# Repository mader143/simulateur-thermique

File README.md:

# Simulateur Thermique
# Équipe 5 (Da best)

## Description

Simulateur thermique 2D pour modéliser la diffusion de chaleur dans une plaque métallique. Le projet regroupe une simulation numérique en Python avec interface graphique PyQt5, une simulation du système et du régulateur via Simulink (Matlab), du code Arduino pour l'acquisition et la régulation d'un prototype réel, et les données expérimentales pour la validation des différents paramètres identifiés.

## Contenu du projet

**Simulation Python** : Résolution par différences finies de l'équation de diffusion thermique, interface utilisateur interactive, génération de résultats et animations.

**Simulation Simulink** : Division du système/procédé en sous-systèmes et identification des fonctions de transfert de ceux-ci. Ajout d'un régulateur PID pour valider la commande contrôlant le prototype.

**Code Arduino** : Contrôleur PID pour régulation thermique, conditionnement des signaux, identification expérimentale, enregistrement des données.

**Conception PCB** : Schémas et circuits imprimés KiCad avec Arduino Mega 2560, amplificateurs opérationnels, et conditionnement analogique pour la lecture de la température en trois points sur la plaque métallique.

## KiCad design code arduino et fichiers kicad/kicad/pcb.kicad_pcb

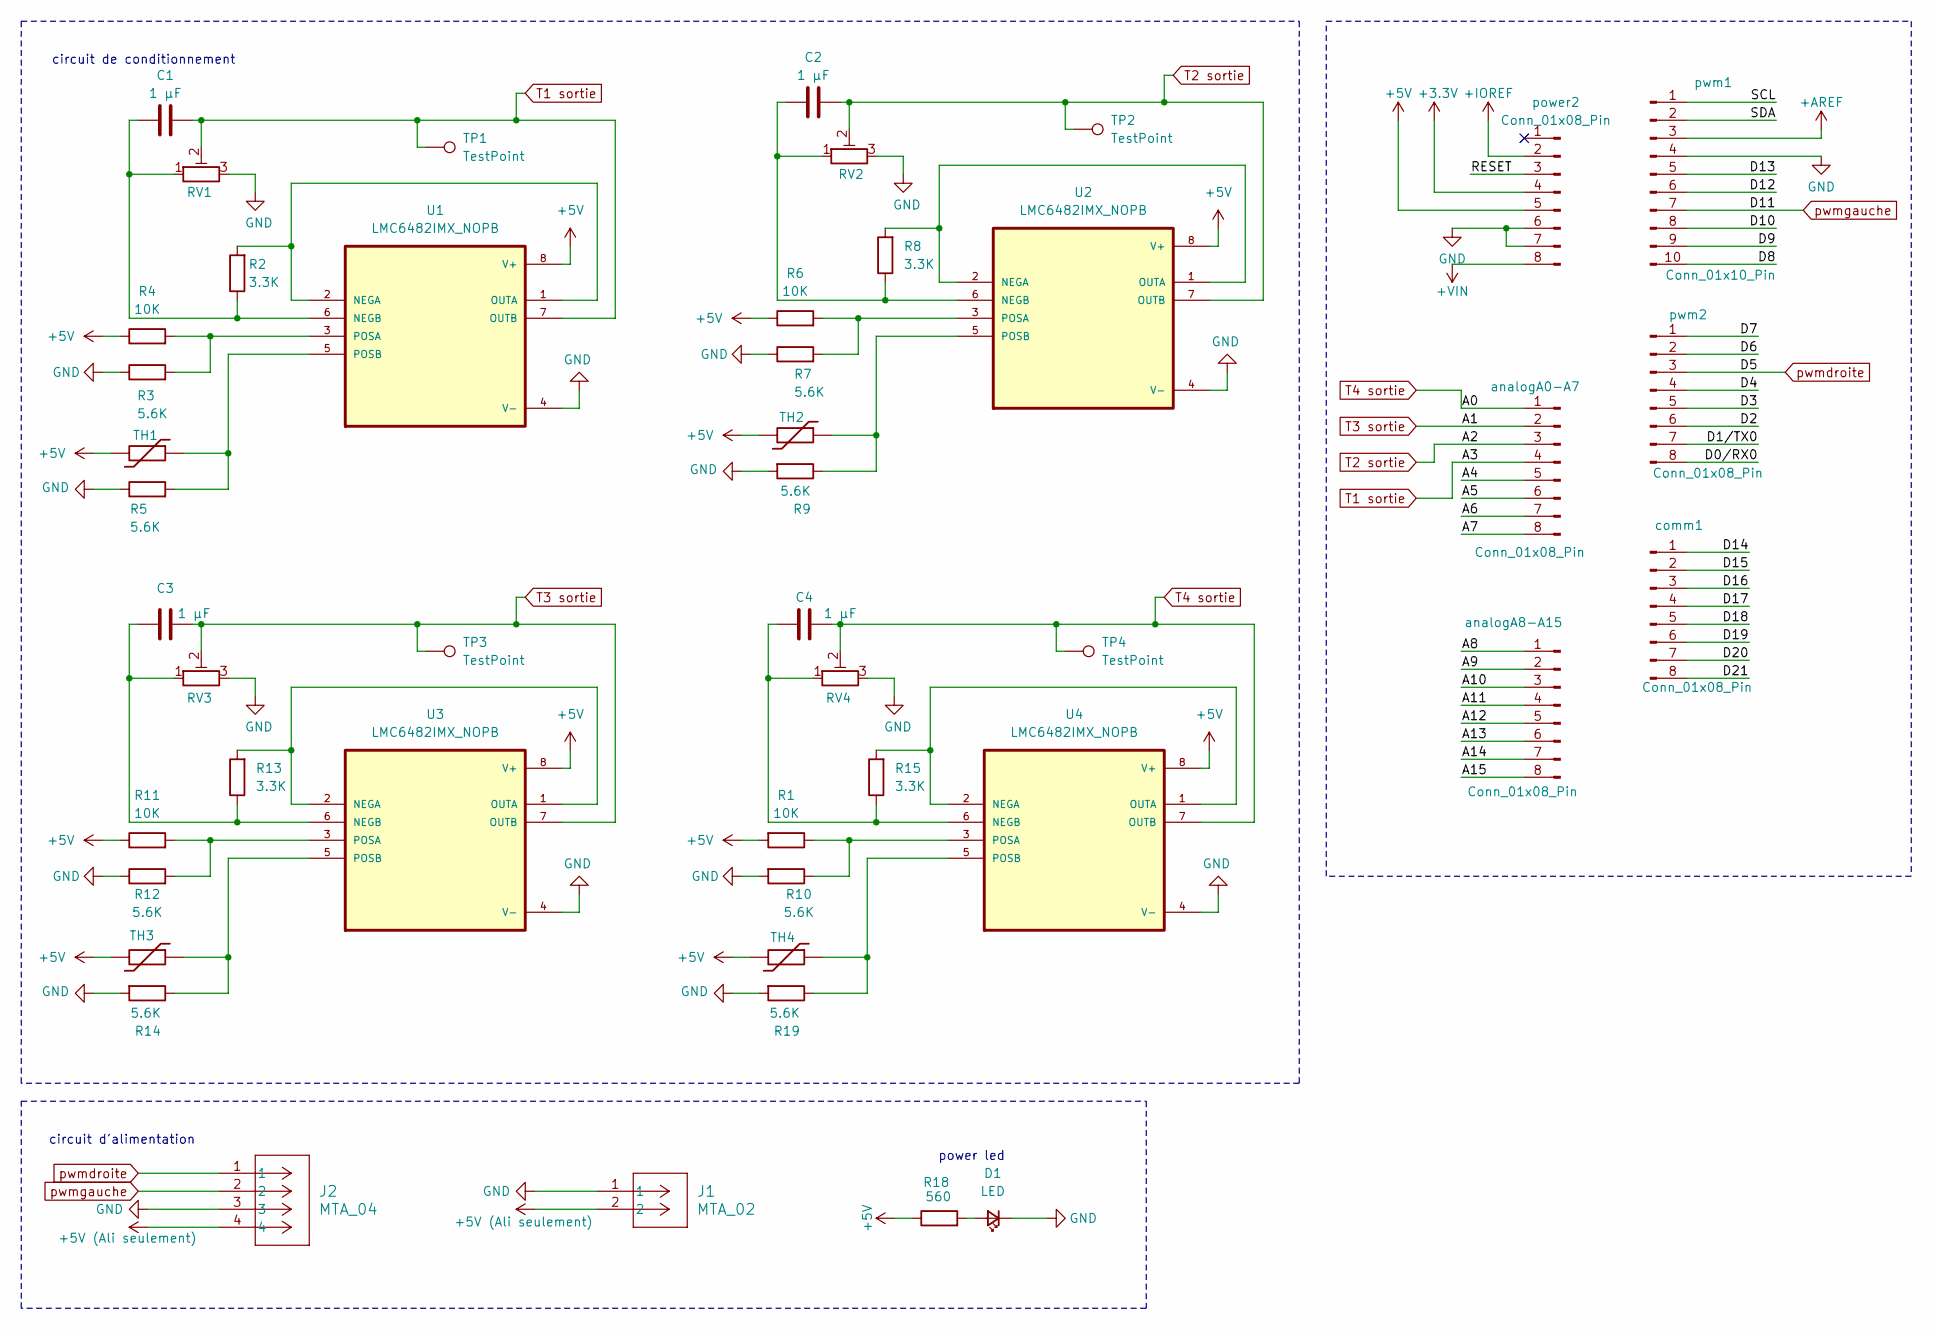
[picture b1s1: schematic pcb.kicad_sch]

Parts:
C1, C2, C3, C4: 1 μF; condensateur 1uF
D1: LED; LED_D5.0mm
J1: MTA_02; MTA_CONN2_640445-2
J2: MTA_04; MTA_CONN4_640445-4
R1, R4, R6, R11: 10K; Resistance SMT
R2, R8, R13, R15: 3.3K; Resistance SMT
R3, R5, R7, R9, R10, R12, R14, R19: 5.6K; Resistance SMT
R18: 560; Resistance SMT
RV1, RV2, RV3, RV4: R_Potentiometer_Trim; trimpot
TH1, TH2, TH3, TH4: Screw_Terminal_01x02; MTA_CONN2_640445-2
TP1, TP2, TP3, TP4: TestPoint; TestPoint_THTPad_D1.5mm_Drill0.7mm
U1, U2, U3, U4: LMC6482IMX_NOPB; LMC6482_SMT
analogA0-A7, analogA8-A15: Conn_01x08_Pin; PinHeader_1x08_P2.54mm_Vertical
comm1: Conn_01x08_Pin; PinHeader_1x08_P2.54mm_Vertical
power2: Conn_01x08_Pin; PinHeader_1x08_P2.54mm_Vertical
pwm1: Conn_01x10_Pin; PinHeader_1x10_P2.54mm_Vertical
pwm2: Conn_01x08_Pin; PinHeader_1x08_P2.54mm_Vertical

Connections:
+3.3V: power2.4
+5V: R1.2, R4.1, R6.1, R11.1, R18.1, TH1.2, TH2.2, TH3.2, TH4.2, U1.8 (V+), U2.8 (V+), U3.8 (V+), U4.8 (V+), power2.5
+5V (Ali seulement): J1.2, J2.4
+AREF: pwm1.3
+IOREF: power2.2
+VIN: power2.8
/A4: analogA0-A7.5
/A5: analogA0-A7.6
/A6: analogA0-A7.7
/A7: analogA0-A7.8
/A8: analogA8-A15.1
/A9: analogA8-A15.2
/A10: analogA8-A15.3
/A11: analogA8-A15.4
/A12: analogA8-A15.5
/A13: analogA8-A15.6
/A14: analogA8-A15.7
/A15: analogA8-A15.8
/D0/RX0: pwm2.8
/D1/TX0: pwm2.7
/D2: pwm2.6
/D3: pwm2.5
/D4: pwm2.4
/D6: pwm2.2
/D7: pwm2.1
/D8: pwm1.10
/D9: pwm1.9
/D10: pwm1.8
/D12: pwm1.6
/D13: pwm1.5
/D14: comm1.1
/D15: comm1.2
/D16: comm1.3
/D17: comm1.4
/D18: comm1.5
/D19: comm1.6
/D20: comm1.7
/D21: comm1.8
/RESET: power2.3
/SCL: pwm1.1
/SDA: pwm1.2
GND: D1.1 (K), J1.1, J2.3, R3.1, R5.1, R7.1, R9.2, R10.2, R12.1, R14.2, R19.2, RV1.3, RV2.3, RV3.3, RV4.3, U1.4 (V-), U2.4 (V-), U3.4 (V-), U4.4 (V-), power2.6, power2.7, pwm1.4
unnamed: D1.2 (A), R18.2
unnamed: R2.2, U1.1 (OUTA), U1.2 (NEGA)
unnamed: C1.1, R2.1, RV1.1, U1.6 (NEGB)
unnamed: R3.2, R4.2, U1.3 (POSA)
unnamed: R5.2, TH1.1, U1.5 (POSB)
unnamed: R8.2, U2.1 (OUTA), U2.2 (NEGA)
unnamed: C2.1, R8.1, RV2.1, U2.6 (NEGB)
unnamed: R6.2, R7.2, U2.3 (POSA)
unnamed: R9.1, TH2.1, U2.5 (POSB)
unnamed: R13.2, U3.1 (OUTA), U3.2 (NEGA)
unnamed: C3.1, R13.1, RV3.1, U3.6 (NEGB)
unnamed: R11.2, R12.2, U3.3 (POSA)
unnamed: R14.1, TH3.1, U3.5 (POSB)
unnamed: R15.2, U4.1 (OUTA), U4.2 (NEGA)
unnamed: C4.1, R15.1, RV4.1, U4.6 (NEGB)
unnamed: R1.1, R10.1, U4.3 (POSA)
unnamed: R19.1, TH4.1, U4.5 (POSB)
T1 sortie: C1.2, RV1.2, TP1.1, U1.7 (OUTB), analogA0-A7.4
T2 sortie: C2.2, RV2.2, TP2.1, U2.7 (OUTB), analogA0-A7.3
T3 sortie: C3.2, RV3.2, TP3.1, U3.7 (OUTB), analogA0-A7.2
T4 sortie: C4.2, RV4.2, TP4.1, U4.7 (OUTB), analogA0-A7.1
pwmdroite: J2.1, pwm2.3
pwmgauche: J2.2, pwm1.7

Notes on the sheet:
circuit d'alimentation
power led
circuit de conditionnement

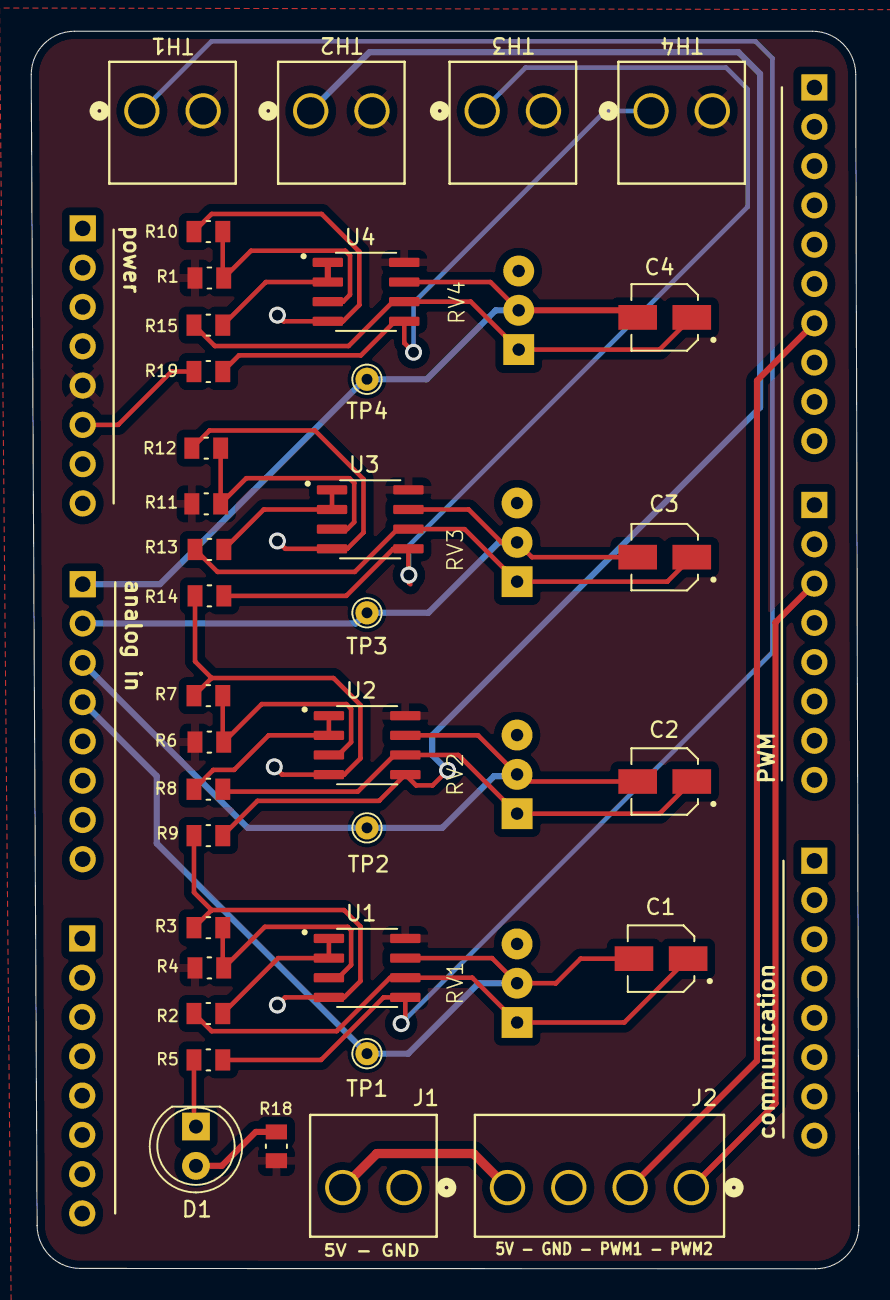
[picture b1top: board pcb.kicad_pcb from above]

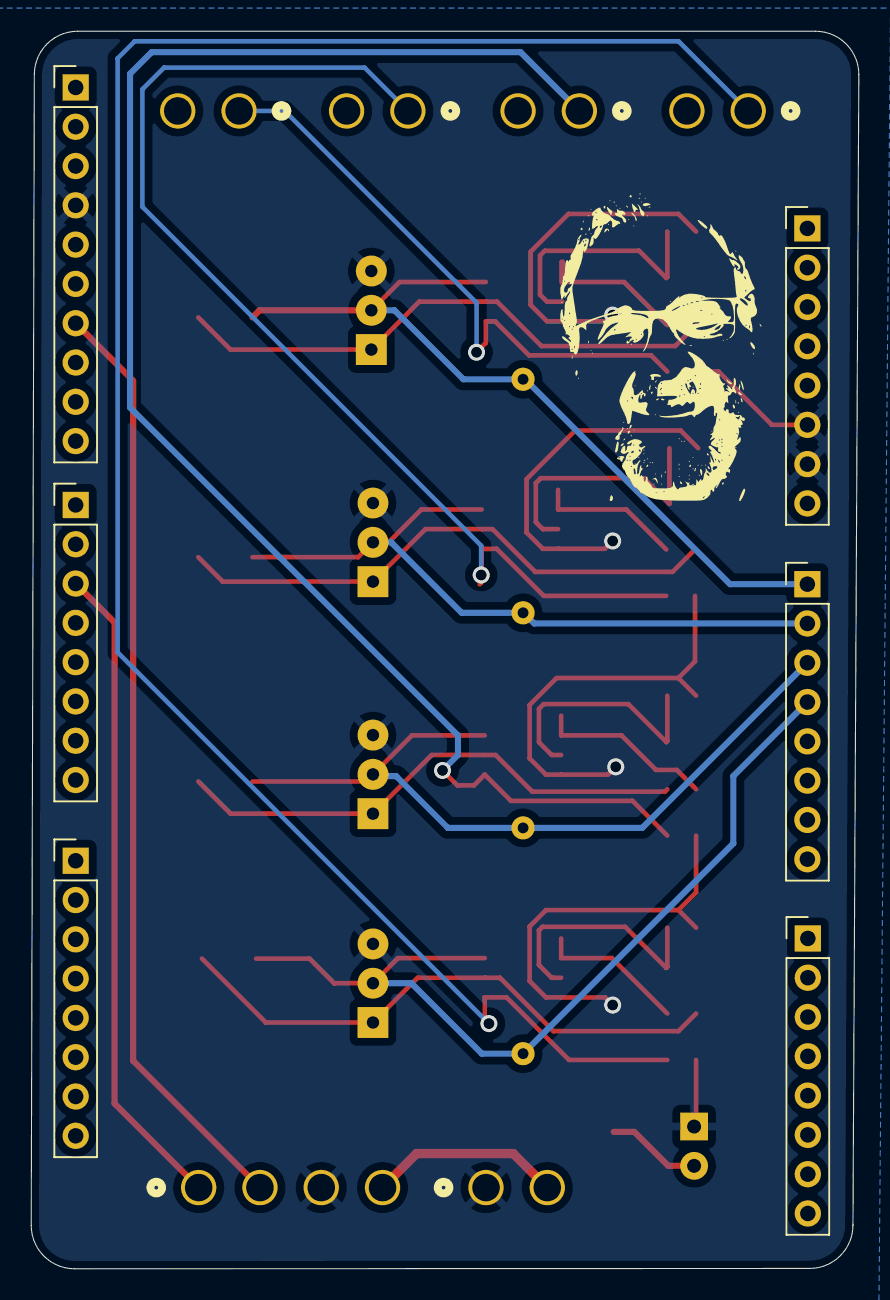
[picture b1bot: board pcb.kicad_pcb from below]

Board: 2 copper layers, 53.5 x 80.0 mm, 46 parts (6 on the bottom side), 26 nets.

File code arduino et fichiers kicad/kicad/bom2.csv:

"Id";"Référence";"Empreinte";"Quantité";"Désignation";"Fournisseur et réf";
1;"RV3,RV2,RV4,RV1";"trimpot";4;"R_Potentiometer_Trim";;;
2;"J1";"MTA_CONN2_640445-2";1;"MTA_02";;;
3;"R6,R4,R11,R1";"Resistance SMT";4;"10K";;;
4;"R3,R10,R14,R9,R5,R19,R7,R12";"Resistance SMT";8;"5.6K";;;
5;"C1,C4,C2,C3";"condensateur 1uF";4;"1 μF";;;
6;"TH3,TH2,TH4,TH1";"MTA_CONN2_640445-2";4;"Screw_Terminal_01x02";;;
7;"D1";"LED_D5.0mm";1;"LED";;;
8;"U1,U3,U2,U4";"LMC6482_SMT";4;"LMC6482IMX_NOPB";;;
9;"R8,R2,R13,R15";"Resistance SMT";4;"3.3K";;;
10;"R18";"Resistance SMT";1;"560";;;
11;"J2";"MTA_CONN4_640445-4";1;"MTA_04";;;
12;"power2,analogA0-A7,comm1,analogA8-A15,pwm2";"PinHeader_1x08_P2.54mm_Vertical";5;"Conn_01x08_Pin";;;
13;"pwm1";"PinHeader_1x10_P2.54mm_Vertical";1;"Conn_01x10_Pin";;;

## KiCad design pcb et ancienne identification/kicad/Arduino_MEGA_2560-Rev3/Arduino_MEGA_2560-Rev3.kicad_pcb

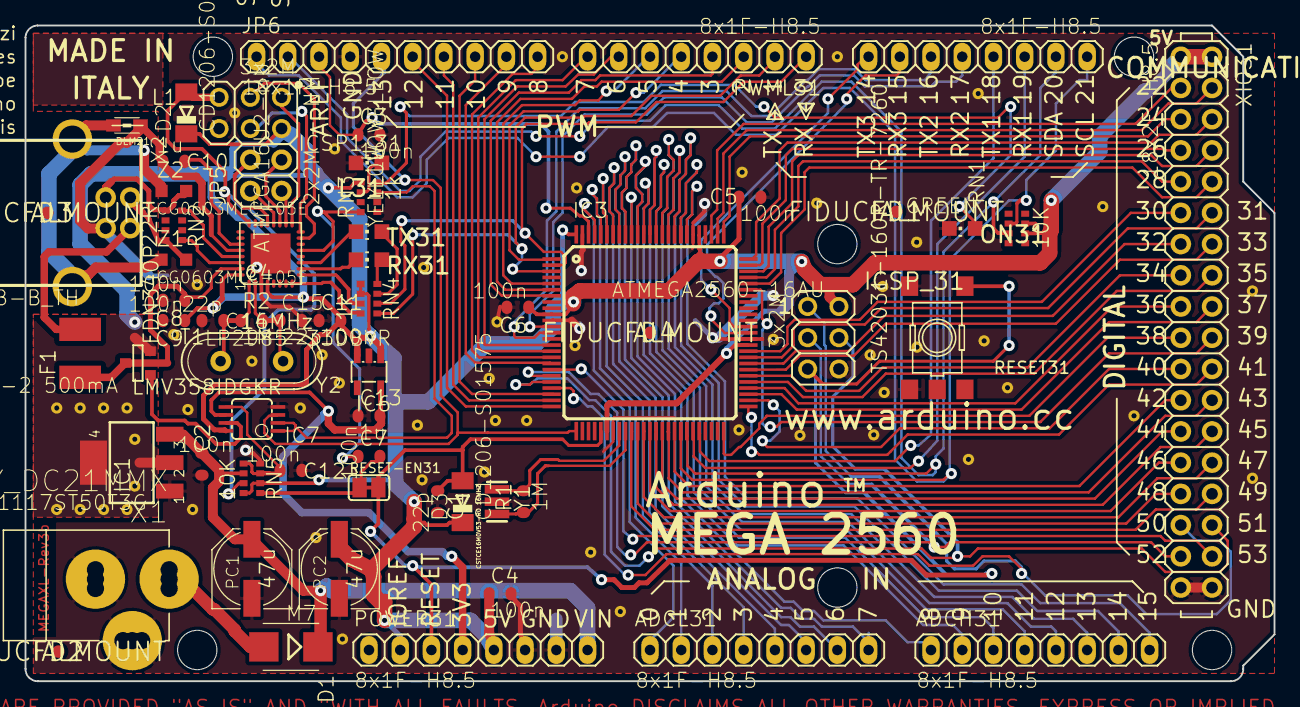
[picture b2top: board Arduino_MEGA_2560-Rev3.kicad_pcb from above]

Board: 2 copper layers, 101.6 x 53.3 mm, 69 parts (1 on the bottom side), 110 nets.

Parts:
@HOLE0, @HOLE1, @HOLE2, @HOLE3, @HOLE4, @HOLE5: (no value)
ADCH31: 8x1F-H8.5; 1X08
ADCL31: 8x1F-H8.5; 1X08
C1, C14, C15: 22p; C0603-ROUND
C2, C3, C4, C5, C6, C7, C8, C9, C11, C12: 100n; C0603-ROUND
C10, C13: 1u; C0603-ROUND
COMMUNICATION31: 8x1F-H8.5; 1X08
D1: M7; SMB
D2, D3: CD1206-S01575; MINIMELF
F1: MF-MSMF050-2 500mA; L1812
FD1, FD2, FD3, FD4: FIDUCIALMOUNT; FIDUCIA-MOUNT
GROUND31: SJ
IC1: NCP1117ST50T3G; SOT223
IC3: ATMEGA2560-16AU; TQFP100
IC4: ATMEGA16U2-MU; MLF32
IC6: LP2985-33DBVR; SOT23-DBV
IC7: LMV358IDGKR; MSOP08
ICSP1_31: 3x2M; 2X03
ICSP_31: 3x2M; 2X03
JP5: 2x2M - NM; 2X02
JP6: 10x1F-H8.5; 1X10
L1: BLM21; 0805
L31: YELLOW; CHIP-LED0805
ON31: GREEN; CHIP-LED0805
PC1, PC2: 47u; PANASONIC_D
POWER31: 8x1F-H8.5; 1X08
PWML31: 8x1F-H8.5; 1X08
R1, R2: 1M; R0603-ROUND
RESET31: TS42031-160R-TR-7260; TS42
RESET-EN31: SJ
RN1, RN5: 10K; CAT16
RN2: 22R; CAY16
RN3, RN4: 1k; CAY16
RX31: YELLOW; CHIP-LED0805
T1: FDN340P; SOT-23
TX31: YELLOW; CHIP-LED0805
U$1: DISCLAIMER
X1: POWERSUPPLY_DC21MMX; POWERSUPPLY_DC-21MM
X2: USB-B_TH; PN61729
XIO31: 18x2F-H8.5; 2X18
Y1: CSTCE16M0V53-R0 16MHZ; RESONATOR
Y2: 16MHz; QS
Z1, Z2: CG0603MLC-05E; CT%2fCN0603

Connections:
+3V3: C13.2, IC6.5, IC7.6, POWER31.4
+5V: C4.1, C5.1, C6.1, C9.1, C11.2, D2.C, D3.C, IC1.2, IC1.4, IC3.10, IC3.31, IC3.61, IC3.80, IC3.100, IC4.4, IC4.32, IC6.1, IC6.3, IC7.8, ICSP1_31.2, ICSP_31.2, PC2.+, POWER31.2, POWER31.5, RN1.6, RN1.7, RN3.1, RN4.5, RN4.6, RN5.2, RN5.8, T1.2, XIO31.1, XIO31.2
/8PB4: IC4.18, JP5.1
/8PB5: IC4.19, JP5.3
/8PB6: IC4.20, JP5.2
/8PB7: IC4.21, JP5.4
/ADC0: ADCL31.1, IC3.97
/ADC1: ADCL31.2, IC3.96
/ADC2: ADCL31.3, IC3.95
/ADC3: ADCL31.4, IC3.94
/ADC4: ADCL31.5, IC3.93
/ADC5: ADCL31.6, IC3.92
/ADC6: ADCL31.7, IC3.91
/ADC7: ADCL31.8, IC3.90
/ADC8: ADCH31.1, IC3.89
/ADC9: ADCH31.2, IC3.88
/ADC10: ADCH31.3, IC3.87
/ADC11: ADCH31.4, IC3.86
/ADC12: ADCH31.5, IC3.85
/ADC13: ADCH31.6, IC3.84
/ADC14: ADCH31.7, IC3.83
/ADC15: ADCH31.8, IC3.82
/AREF: C3.1, IC3.98, JP6.3
/CMP: C12.2, IC7.5, RN5.3, RN5.5
/D+: RN2.5, X2.3, Z2.2
/D-: RN2.8, X2.2, Z1.2
/DTR: C7.1, IC4.13, RN3.4
/GATE_CMD: IC7.7, T1.3
/L13: IC7.1, IC7.2, RN3.7
/M8RXD: IC4.9, RN4.7
/M8TXD: IC4.8, RN4.8
/MISO2: IC4.17, ICSP1_31.1
/MOSI2: IC4.16, ICSP1_31.4
/N$2: L31.A, RN3.2
/N$3: ON31.A, RN3.8
/N$54: RN4.4, RX31.A
/N$55: RN4.3, TX31.A
/PA0: IC3.78, XIO31.3
/PA1: IC3.77, XIO31.4
/PA2: IC3.76, XIO31.5
/PA3: IC3.75, XIO31.6
/PA4: IC3.74, XIO31.7
/PA5: IC3.73, XIO31.8
/PA6: IC3.72, XIO31.9
/PA7: IC3.71, XIO31.10
/PB0: IC3.19, XIO31.34
/PB1: IC3.20, ICSP_31.3, XIO31.33
/PB2: IC3.21, ICSP_31.4, XIO31.32
/PB3: IC3.22, ICSP_31.1, XIO31.31
/PB4: IC3.23, JP6.8
/PB5: IC3.24, JP6.7
/PB6: IC3.25, JP6.6
/PB7: IC3.26, IC7.3, JP6.5
/PC0: IC3.53, XIO31.18
/PC1: IC3.54, XIO31.17
/PC2: IC3.55, XIO31.16
/PC3: IC3.56, XIO31.15
/PC4: IC3.57, XIO31.14
/PC5: IC3.58, XIO31.13
/PC6: IC3.59, XIO31.12
/PC7: IC3.60, XIO31.11
/PD7: IC3.50, XIO31.19
/PE0: IC3.2, PWML31.1, RN4.2
/PE1: IC3.3, PWML31.2, RN4.1
/PE3: IC3.5, PWML31.6
/PE4: IC3.6, PWML31.3
/PE5: IC3.7, PWML31.4
/PG0: IC3.51, XIO31.22
/PG1: IC3.52, XIO31.21
/PG2: IC3.70, XIO31.20
/PG5: IC3.1, PWML31.5
/PH3: IC3.15, PWML31.7
/PH4: IC3.16, PWML31.8
/PH5: IC3.17, JP6.10
/PH6: IC3.18, JP6.9
/PL0: IC3.35, XIO31.30
/PL1: IC3.36, XIO31.29
/PL2: IC3.37, XIO31.28
/PL3: IC3.38, XIO31.27
/PL4: IC3.39, XIO31.26
/PL5: IC3.40, XIO31.25
/PL6: IC3.41, XIO31.24
/PL7: IC3.42, XIO31.23
/PWRIN: D1.A, X1.2
/RD+: IC4.29, RN2.4
/RD-: IC4.30, RN2.1
/RESET: C1.1, C7.2, D3.A, IC3.30, ICSP_31.5, POWER31.3, RESET31.3, RESET31.4, RESET-EN31.1, RESET-EN31.2, RN5.1
/RESET2: D2.A, IC4.24, ICSP1_31.5, RN5.7
/RXD1: COMMUNICATION31.3, IC3.45
/RXD2: COMMUNICATION31.5, IC3.12
/RXD3: COMMUNICATION31.7, IC3.63
/RXL: IC4.10, RX31.C
/SCK2: IC4.15, ICSP1_31.3
/SCL: COMMUNICATION31.1, IC3.43, JP6.1, RN1.2
/SDA: COMMUNICATION31.2, IC3.44, JP6.2, RN1.3
/TXD1: COMMUNICATION31.4, IC3.46
/TXD2: COMMUNICATION31.6, IC3.13
/TXD3: COMMUNICATION31.8, IC3.64
/TXL: IC4.11, TX31.C
/UGND: C10.2, GROUND31.1, IC4.28, L1.1, X2.4
/USBVCC: C8.1, F1.1, IC4.31, T1.1
/USHIELD: L1.2, X2.P$1, X2.P$2, Z1.1, Z2.1
/VIN: C2.1, D1.C, IC1.3, PC1.+, POWER31.8, RN5.6
/VUCAP: C10.1, IC4.27
/XT1: C14.1, IC4.1, R2.1, Y2.2
/XT2: C15.1, IC4.2, R2.2, Y2.1
/XTAL1: IC3.34, R1.1, Y1.3
/XTAL2: IC3.33, R1.2, Y1.1
/XVCC: F1.2, X2.1
GND: C1.2, C2.2, C3.2, C4.2, C5.2, C6.2, C8.2, C9.2, C11.1, C12.1, C13.1, C14.2, C15.2, GROUND31.2, IC1.1, IC3.11, IC3.32, IC3.62, IC3.81, IC3.99, IC4.3, IC4.33, IC6.2, IC7.4, ICSP1_31.6, ICSP_31.6, JP6.4, L31.C, ON31.C, PC1.-, PC2.-, POWER31.6, POWER31.7, RESET31.1, RESET31.2, RN3.5, RN5.4, X1.1, X1.3, XIO31.35, XIO31.36, Y1.2

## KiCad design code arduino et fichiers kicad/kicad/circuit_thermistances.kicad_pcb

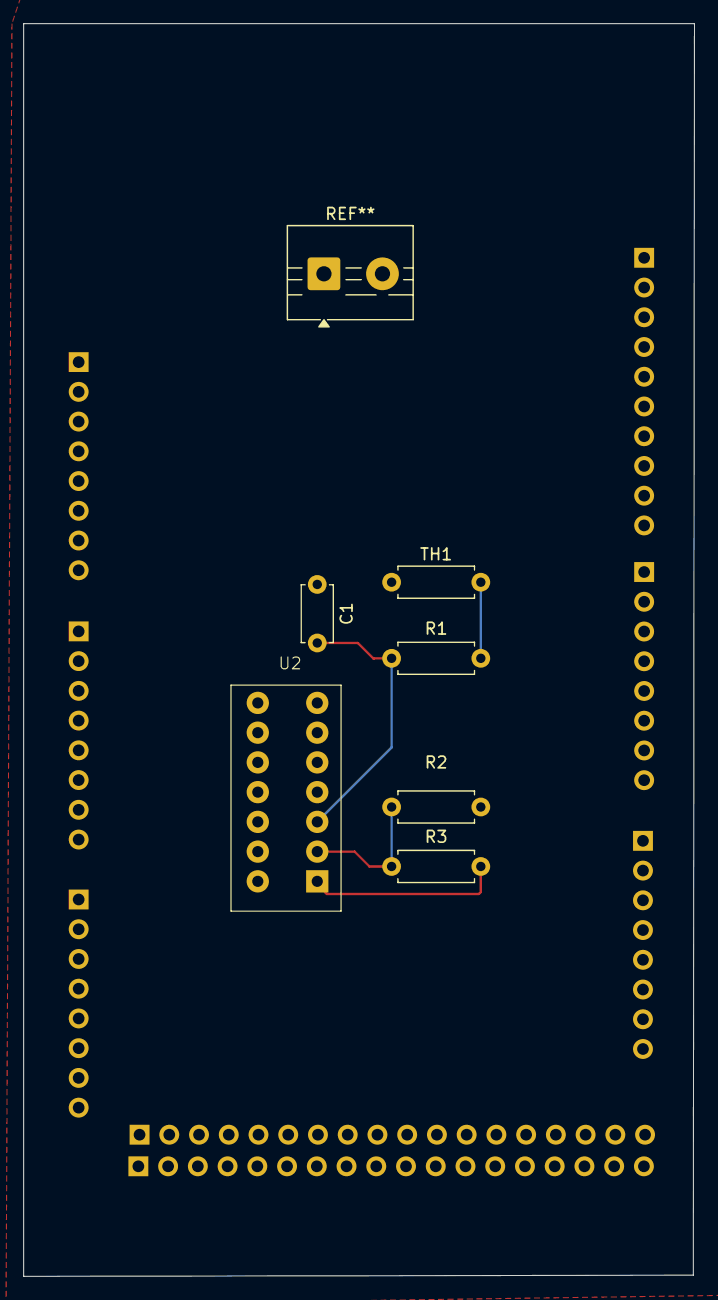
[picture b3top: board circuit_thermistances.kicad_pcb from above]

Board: 4 copper layers, 57.3 x 107.0 mm, 6 parts (0 on the bottom side), 5 nets.

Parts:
C1: 100n; C_Disc_D4.7mm_W2.5mm_P5.00mm
R1, R2, R3: 10K; R_Axial_DIN0207_L6.3mm_D2.5mm_P7.62mm_Horizontal
TH1: 10K; R_Axial_DIN0207_L6.3mm_D2.5mm_P7.62mm_Horizontal
U2: LMC6484

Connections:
GND: C1.1, R2.1, TH1.2
unnamed: R3.1, U2.1
unnamed: R1.1, TH1.1
unnamed: C1.2, R1.2, U2.3 (+)
unnamed: R2.2, R3.2, U2.2 (-)

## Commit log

2026-01-19 test commit
2026-01-19 test commit1
2026-01-19 testmia
2026-01-19 test a
2026-01-20 debut fonction plaque
2026-01-20 test pypde
2026-01-20 fx plaque
2026-01-20 ajout
2026-01-20 test code trouvé en ligne
2026-01-20 commentaires
2026-01-20 commentaires 2
2026-01-21 code matlab en python
2026-01-22 changements
2026-01-22 start
2026-01-24 hjdsfjh
2026-01-24 ca marche pas
2026-01-24 vectorisé
2026-01-24 graphiques updates
2026-01-24 marche bien
2026-01-24 warning
2026-01-26 essai 100s
2026-01-28 jksdb
2026-01-28 bhdj
2026-01-28 dnjkd
2026-01-29 jkabsf
2026-01-29 je crois que cest plus realiste la
2026-01-29 temps reel
2026-01-29 eeee
2026-01-30 save interval
2026-01-30 interface
2026-01-31 ughhh jai aucune idee
2026-02-01 jai essayé deux méthodes pour les bords et les deux sont mid alors jsp frl...
2026-02-01 dskjbcd
2026-02-01 début de l'interface graphique
2026-02-01 jfke
2026-02-02 charger données json dans interface
2026-02-02 nvm ca fonctionnait cetait mon ordi le probleme
2026-02-02 waiiiit
2026-02-04 MEGA commit
2026-02-04 Enregistrement csv
2026-02-04 test kicad
2026-02-04 circuitver1
2026-02-04 ajout kicad
2026-02-04 Csv fonctionnel
2026-02-04 valeurs resistances
2026-02-04 Graphique du csv fonctionnel
2026-02-04 oops
2026-02-04 ca marche pas pantoute
2026-02-04 mega^2 commit
2026-02-04 noms de pins arduino
2026-02-04 nvjkdskjn
2026-02-04 bjkwds
2026-02-04 njvkds
2026-02-04 identification thermistances!
2026-02-05 test claude
2026-02-05 test_claude_suite
2026-02-05 debut pcb
2026-02-05 kasjd
2026-02-05 njksd
2026-02-06 procrastination pendant optique
2026-02-07 ajout d'un readme because.......
2026-02-07 Add gitignore
2026-02-07 ksjkasjdh
2026-02-08 pcb yaddi yadda
2026-02-09 version tht pour pas trop haïr notre vie plus tard
2026-02-09 kjdsjhvdshj
2026-02-09 fnsdljnf
2026-02-09 Changment connecteur pcb
2026-02-09 test
2026-02-09 Pcb quasi fini
2026-02-09 PCB + BOM
2026-02-10 PCB partie 4, bom fini ?
2026-02-10 Avancer l'interface graphique : - Implémenté un thread - Mis la nouvelle façon de simuler dans SimulationThermique - Créé et mis dans l'interface des widgets matplotlib qui devraient pouvoir graph le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
2026-02-10 matlab
2026-02-10 njkw
2026-02-10 cefw
2026-02-10 Changements connecteurs
2026-02-10 PC V2 fini
2026-02-11 test matlab
2026-02-11 Commit Vmille
2026-02-11 PCB V2 - Envoyé à Martin
2026-02-11 mercredi
2026-02-11 njkds
2026-02-11 planif achat pcb
2026-02-11 graph 3 thermistances
2026-02-11 correction graph
2026-02-11 simulation
2026-02-11 Avancer l'interface graphique :
2026-02-11 modif graphique
2026-02-11 G1G2G3
2026-02-12 print
2026-02-12 données
2026-02-13 incertitudes
2026-02-15 Modifs valeur R schematic
2026-02-15 echelon
2026-02-16 lecture 3 thermistances
2026-02-16 modif thermistance individuelle
2026-02-16 code (à calibrer)
2026-02-16 lundi
2026-02-16 h trouvé yééééé
2026-02-18 pourh
2026-02-18 dgsv
2026-02-18 curvefit
2026-02-18 point op et systeme complet
2026-02-18 Tests puissance code
2026-02-18 merge
2026-02-18 hkha
2026-02-18 powarrrr
2026-02-18 bleh
2026-02-18 rechaud
2026-02-18 bhdahs
2026-02-18 destination
2026-02-18 njkdsv
2026-02-18 bjkvs
2026-02-18 vsdv
2026-02-18 graphique
2026-02-19 njfe
2026-02-20 graphique puissance
2026-02-20 pidfffff
2026-02-20 regression pour valeur B
2026-02-20 changement endroit fichier
2026-02-20 12.5
2026-02-20 puissance 12.5
2026-02-21 simumumu
2026-02-24 vsvd
2026-02-25 fdjhj
2026-02-25 trytr
2026-02-25 organisation simulink
2026-02-25 modification de l'interface graphique, ajout d'un timer et des 3 thermistances sur le graphique
2026-02-25 timer updaté, enlever l'erreur
2026-02-25 interface fonctionnelle, problème de la figure 3d à enlever...
2026-02-25 hgfj
2026-02-25 nonetype
2026-02-25 jhgj
2026-02-25 no nonetype #2
2026-02-25 oups
2026-02-25 esti de kicad
2026-02-27 PCB V2
2026-02-27 Gerber files exportés, on commande?
2026-02-28 silkscreen
2026-02-28 V4 zip file
2026-03-01 test pid
2026-03-01 njkvds
2026-03-03 changement du thread par un QTimer. Permet d'enlever l'erreur qui était causée par la façon d'implanter la méthode dans le thread mais aussi d'update les graphiques au fur et à mesure (pcq dans le th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
2026-03-03 Tout plein de choses!!! Notamment: - Sauvegarder les résultats - Changer la position des thermistances - Messages d'erreurs pour prévenir les bogues - Changement du layout
    L'interface est pas mal complétée à ce stade-ci :)
2026-03-04 rajouté les titres d'axes dans les graphiques
2026-03-04 lecture+pid combiné code arduino pour asservissement
2026-03-05 asservissement avec arduino test du code avec une consigne de 28, une perturbation qui rechauffe, une perturbation qui refroidit
2026-03-05 ptites erreurs dans les axes oupsi
2026-03-06 timer
2026-03-08 jhkjh
2026-03-08 test simulink
    changements DAC, TEC, PID et ajout convection
2026-03-09 clean up
2026-03-09 timer correction
2026-03-09 modification du code asservissement incluant estimation de 3
2026-03-09 code pour discrétiser la tf du pid
2026-03-09 Sauvegardes mineurs kicad et BOM
2026-03-10 génération de graphique après asservissement
2026-03-11 interface proto
2026-03-11 test interface proto
2026-03-11 test2 interface proto
2026-03-11 Instructions PlatformIO
2026-03-12 interface correction
2026-03-12 pid avec esti de estimation
2026-03-12 ajustement_boutons_proto
2026-03-12 interface visuel fini?
2026-03-13 gros update asservissement: - changement d'endroit de certains fichiers - identification des trois thermistances en chauffant/refroidissant avec petite/grande commande (à retester avec commande de 30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
2026-03-13 simulink
2026-03-14 sauvegarder les données de température de la plaque sur plusieurs temps
2026-03-15 comm arduino
2026-03-15 trouver le port automatiquement
2026-03-16 dino
2026-03-16 t3 interface
2026-03-16 main interface
2026-03-16 reorganisation
2026-03-16 erreur et commande
2026-03-16 modified: Proto_interface/src/interface.py
2026-03-16 oups erreur petite modif
2026-03-16 une autre petite modif
2026-03-16 encore modif
2026-03-16 simulink16marshihi
2026-03-16 2 graph
2026-03-16 simulink16marshihi
    pid pour le refroidissement, boucle if avec chauffage et refroidissement, tout dans un seul scope! YAA
2026-03-17 comm arduino, pid
2026-03-17 données de lundi
2026-03-18 Changement de la boucle simulink
    Réorganisation, choix pour la convection, ajustement automatique de la temp. initiale et de la consigne
2026-03-18 bkjh
2026-03-18 nmcd
2026-03-18 arreter proto
2026-03-18 arreterproto2
2026-03-18 hahs
2026-03-18 jkhdjk
2026-03-18 code pour pid refroidissement
2026-03-18 relations a
2026-03-18 changement code pour pid refroidissement
2026-03-18 pid refroid
2026-03-18 reltions a
2026-03-19 interface overkill
2026-03-19 test interface
2026-03-19 modifs
2026-03-19 test pour reset graphiques interface proto
2026-03-19 test pour reset graphiques interface proto 2
2026-03-19 wouhou les graphiques updatent
2026-03-20 interface (final)
2026-03-20 corrections interface
2026-03-20 pid froid chaud code Arduino test
2026-03-20 simulink20marshihi
    pid un peu plus brusque pour le refroidissement
2026-03-20 inerface quasi final
2026-03-20 fix axe commande
2026-03-20 Fichier Arduino qui fonctionne bien, on a changé: - u_prev = u quand pas saturé - reset des u_prev et e[1], e[2] quand on applique une nouvelle configuration. On lit pas les bonnes températures des t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
    On print les lignes de l'Arduino dans le terminal aussi! En mode débogage :o
2026-03-20 applied
2026-03-20 interface petit changement de code
2026-03-20 esthétique interface
2026-03-20 cleanup
2026-03-20 esthetique encore oups
2026-03-21 code arduino pour envoyer pwm et print la tension lue par l'Arduino à la thermistance
2026-03-21 mini modif
2026-03-21 modification du main pour reset le temps écoulé à 0 quand on applique une nouvelle commande
2026-03-21 gfkj
2026-03-21 modification du main encore
2026-03-22 correction consigne enregistrement des donnees
2026-03-23 appliquer pwm
2026-03-23 mode manuel + absolute value
2026-03-23 mode manuel
2026-03-23 T1 changement
2026-03-23 petites modifs
2026-03-23 impression schéma électrique pour éval prototype
2026-03-23 erreur fix
2026-03-23 reparations
2026-03-23 modification du main pour mode manuel
2026-03-23 excel (ugh)
2026-03-24 vjkhgk
2026-03-24 evaluation prototype
2026-03-29 validation et résultats du simulateur
2026-04-01 enregistrement pu de bug
2026-04-01 paramètres des interfaces
2026-04-01 simul boucle ouverte
2026-04-01 SIMULINK QUI MARCHE
2026-04-01 prise des mesures pour le prototype en boucle ouverte (rapport 3)
2026-04-03 ajout interface simulinl
2026-04-03 amélioration simulink - interface (clicker sur apply, puis lance la simulation, pour voir blocs, clicker sur petite flêche en bas à gauche du mask) - possibilité de modification des paramètres - enre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
    Reste à faire:
    - nouvelle ident pour refroidissement aussi
    - ajout de perturbations
    - faire une ident pour procédé excepté thermistance, puis ensuite décomposé la thermistance avec la formule
2026-04-03 régalge bug lors du changement des dimensions de la plaque dans la simulation thermique
2026-04-04 commentaires simu thermique
2026-04-04 ajout de position de l'actuateur
2026-04-04 perturbation
2026-04-04 position et puissance de perturbation
2026-04-04 changement du temps d'application
2026-04-04 perturb changement
2026-04-04 moment d'allumage de l'actionneur
2026-04-04 correction puissance negative
2026-04-05 coeff json
2026-04-05 graphique pour identifier la puissance en chauffage et en refroidissement avec les nouvelles données
2026-04-06 prise de données
2026-04-06 enregistrement vt1, vt2 et vt3
2026-04-06 main arduino V
2026-04-06 correction mode manuel
2026-04-06 ident_tension
    workspace, simulink et code identification duty cycle-tension aux thermistances
2026-04-07 Figures pour la simulation python - section 8.1 dans le rapport 3
2026-04-07 données + calculs puissance
2026-04-07 puissance
2026-04-07 7 avril
2026-04-07 identification7avril
2026-04-07 avec puissance
2026-04-07 G des thermistances avec puissance + essai tf
2026-04-08 manuel d'utilisation en pdf pour le simulateur de chaleur, le word original est dans le teams (si besoin de modifications)
2026-04-08 modif power refroidissement
2026-04-08 modif curvefit
2026-04-08 readme.md simulateur thermique
2026-04-08 modifs affichage
2026-04-08 pour etre sur, simulink test
2026-04-09 boucle ouverte simulink proto
2026-04-09 procede
2026-04-09 ggraphique boucle fermée
2026-04-09 modifs simulink: - pid dans interface - perturbation (à voir au mettre) - saturation
2026-04-09 Boucle ouverte V2
2026-04-09 Code Arduino pid
2026-04-09 V2 code arduino pid
2026-04-09 graphiques boucleouverte
2026-04-09 pid cpp
2026-04-09 code+graphique boucle ouverte / ferme / perturbation
2026-04-09 proto BF
2026-04-09 Update organisation de fichiers
2026-04-09 graphiques boucles ouvertes fermées
2026-04-09 bug commmit
2026-04-09 BF sans perturbation
2026-04-09 graphs_bo_changement de nom
    $$$$
2026-04-09 BF avec pertrbations fini 9 avril
2026-04-09 boucle fermee graphiques
2026-04-09 boucle fermee sans perturbation
2026-04-10 simulink 10 avril
2026-04-10 graphiques supprimés %%%
2026-04-10 ajout des limites sur l'interface python et changement des données pour la puissance
2026-04-10 encore graphiques
2026-04-10 presque finale
2026-04-10 encore graphis
2026-04-10 folder
2026-04-10 have fun mathilde!
2026-04-10 SimControlV2
2026-04-10 vf je crois de la simulation python
2026-04-10 Manuel d'utilisation Simulink
2026-04-10 Manuel d'utilisation final
2026-04-11 recréation des graphiques en BO
2026-04-22 PhotosThermiques_ValidationProto
